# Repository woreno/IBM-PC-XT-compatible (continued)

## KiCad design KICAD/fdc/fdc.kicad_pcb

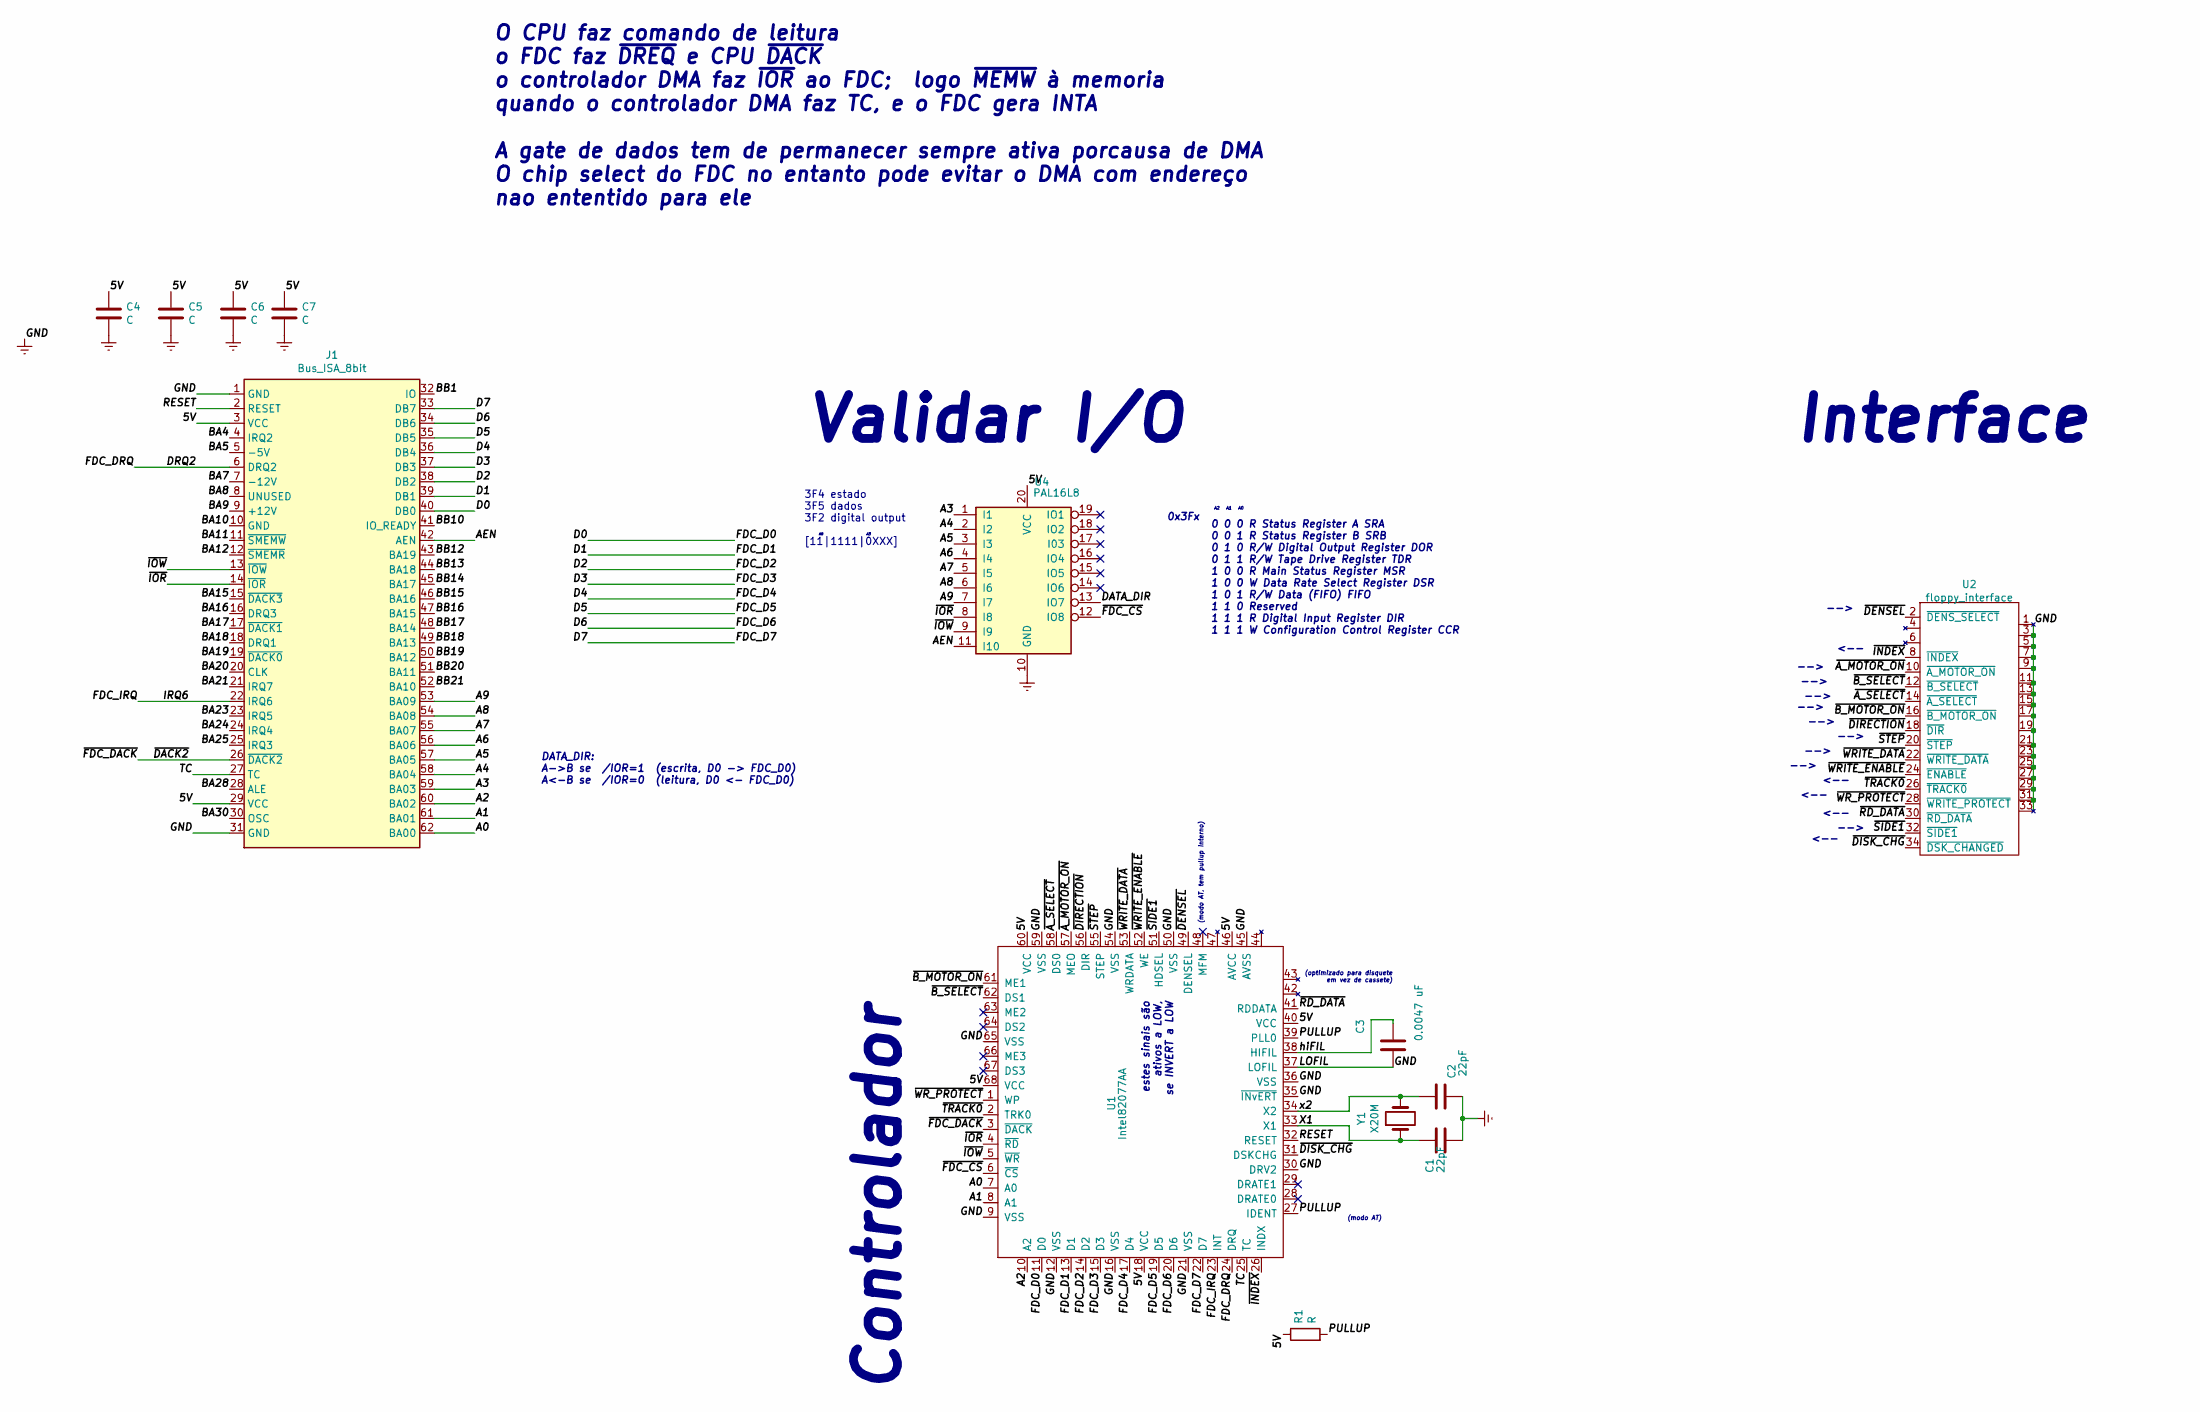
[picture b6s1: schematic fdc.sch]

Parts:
C1: 22pF; standard_2pins
C2: 22pF; standard_2pins_half
C3: 0.0047 uF; standard_2pins
C4, C5, C6: C; standard_2pins
C7: C; standard_2pins_half
J1: Bus_ISA_8bit; ISA_8bit_edge
R1: R; standard_2pins
U1: Intel82077AA; PLCC-68_SMD-Socket
U2: floppy_interface; PinSocket_2x17_P2.54mm_Vertical
U4: PAL16L8; standard_DIP_20pins_thin_body
Y1: X20M; standard_2pins_half

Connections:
/5V: C4.1, C5.1, C6.1, C7.1, J1.3 (VCC), J1.29 (VCC), R1.1, U1.18 (VCC), U1.40 (VCC), U1.46 (AVCC), U1.60 (VCC), U1.68 (VCC), U4.20 (VCC)
/A0: J1.62 (BA00), U1.7 (A0)
/A1: J1.61 (BA01), U1.8 (A1)
/A2: J1.60 (BA02), U1.10 (A2)
/A3: J1.59 (BA03), U4.1 (I1)
/A4: J1.58 (BA04), U4.2 (I2)
/A5: J1.57 (BA05), U4.3 (I3)
/A6: J1.56 (BA06), U4.4 (I4)
/A7: J1.55 (BA07), U4.5 (I5)
/A8: J1.54 (BA08), U4.6 (I6)
/A9: J1.53 (BA09), U4.7 (I7)
/AEN: J1.42 (AEN), U4.11 (I10)
/BA4: J1.4 (IRQ2)
/BA5: J1.5 (-5V)
/BA7: J1.7 (-12V)
/BA8: J1.8 (UNUSED)
/BA9: J1.9 (+12V)
/BA10: J1.10 (GND)
/BA11: J1.11 (~SMEMW)
/BA12: J1.12 (~SMEMR)
/BA15: J1.15 (~DACK3)
/BA16: J1.16 (DRQ3)
/BA17: J1.17 (~DACK1)
/BA18: J1.18 (DRQ1)
/BA19: J1.19 (~DACK0)
/BA20: J1.20 (CLK)
/BA21: J1.21 (IRQ7)
/BA23: J1.23 (IRQ5)
/BA24: J1.24 (IRQ4)
/BA25: J1.25 (IRQ3)
/BA28: J1.28 (ALE)
/BA30: J1.30 (OSC)
/BB1: J1.32 (IO)
/BB10: J1.41 (IO_READY)
/BB12: J1.43 (BA19)
/BB13: J1.44 (BA18)
/BB14: J1.45 (BA17)
/BB15: J1.46 (BA16)
/BB16: J1.47 (BA15)
/BB17: J1.48 (BA14)
/BB18: J1.49 (BA13)
/BB19: J1.50 (BA12)
/BB20: J1.51 (BA11)
/BB21: J1.52 (BA10)
/D0: J1.40 (DB0), U1.11 (D0)
/D1: J1.39 (DB1), U1.13 (D1)
/D2: J1.38 (DB2), U1.14 (D2)
/D3: J1.37 (DB3), U1.15 (D3)
/D4: J1.36 (DB4), U1.17 (D4)
/D5: J1.35 (DB5), U1.19 (D5)
/D6: J1.34 (DB6), U1.20 (D6)
/D7: J1.33 (DB7), U1.22 (D7)
/DATA_DIR: U4.13 (IO7)
/DRQ2: J1.6 (DRQ2), U1.24 (DRQ)
/FDC_IRQ: J1.22 (IRQ6), U1.23 (INT)
/PULLUP: R1.2, U1.27 (IDENT), U1.39 (PLL0)
/RESET: J1.2 (RESET), U1.32 (RESET)
/TC: J1.27 (TC), U1.25 (TC)
/X1: C1.1, U1.33 (X1), Y1.1
/hiFIL: C3.1, U1.38 (HIFIL)
/x2: C2.2, U1.34 (X2), Y1.2
/~A_MOTOR_ON: U1.57 (MEO), U2.10 (~A_MOTOR_ON)
/~A_SELECT: U1.58 (DS0), U2.14 (~A_SELECT)
/~B_MOTOR_ON: U1.61 (ME1), U2.16 (~B_MOTOR_ON)
/~B_SELECT: U1.62 (DS1), U2.12 (~B_SELECT)
/~DACK2: J1.26 (~DACK2), U1.3 (~DACK)
/~DENSEL: U1.49 (DENSEL), U2.2 (~DENS_SELECT)
/~DIRECTION: U1.56 (DIR), U2.18 (~DIR)
/~DISK_CHG: U1.31 (DSKCHG), U2.34 (~DSK_CHANGED)
/~FDC_CS: U1.6 (~CS), U4.12 (IO8)
/~INDEX: U1.26 (INDX), U2.8 (~INDEX)
/~IOR: J1.14 (~IOR), U1.4 (~RD), U4.8 (I8)
/~IOW: J1.13 (~IOW), U1.5 (~WR), U4.9 (I9)
/~RD_DATA: U1.41 (RDDATA), U2.30 (~RD_DATA)
/~SIDE1: U1.51 (HDSEL), U2.32 (~SIDE1)
/~STEP: U1.55 (STEP), U2.20 (~STEP)
/~TRACK0: U1.2 (TRK0), U2.26 (~TRACK0)
/~WRITE_DATA: U1.53 (WRDATA), U2.22 (~WRITE_DATA)
/~WRITE_ENABLE: U1.52 (WE), U2.24 (~ENABLE)
/~WR_PROTECT: U1.1 (WP), U2.28 (~WRITE_PROTECT)
Earth: C1.2, C2.1, C3.2, C4.2, C5.2, C6.2, C7.2, J1.1 (GND), J1.31 (GND), U1.9 (VSS), U1.12 (VSS), U1.16 (VSS), U1.21 (VSS), U1.30 (DRV2), U1.35 (~INvERT), U1.36 (VSS), U1.37 (LOFIL), U1.45 (AVSS), U1.50 (VSS), U1.54 (VSS), U1.59 (VSS), U1.65 (VSS), U2.1, U2.3, U2.5, U2.7, U2.9, U2.11, U2.13, U2.15, U2.17, U2.19, U2.21, U2.23, U2.25, U2.27, U2.29, U2.31, U2.33, U4.10 (GND)

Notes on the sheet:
0 0 0 R Status Register A SRA 0 0 1 R Status Register B SRB 0 1 0 R/W Digital Output Register DOR 0 1 1 R/W Tape Drive Register TDR 1 0 0 R Main Status Register MSR 1 0 0 W Data Rate Select Register DSR 1 0 1 R/W Data (FIFO) FIFO 1 1 0 Reserved 1 1 1 R Digital Input Register DIR 1 1 1 W Configurati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
A2 A1 A0
0x3Fx
(modo AT)
estes sinais são ativos a LOW, se INVERT a LOW
(modo AT, tem pullup interno)
(optimizado para disquete em vez de cassete)
3F4 estado 3F5 dados 3F2 digital output [11|1111|0XXX]
<--
-->
Controlador
Interface
Validar I/O
O CPU faz comando de leitura o FDC faz ~DREQ~ e CPU ~DACK~ o controlador DMA faz ~IOR~ ao FDC; logo ~MEMW~ à memoria quando o controlador DMA faz TC, e o FDC gera INTA A gate de dados tem de permanecer sempre ativa porcausa de DMA O chip select do FDC no entanto pode evitar o DMA com endereço nao e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
DATA_DIR: A->B se /IOR=1 (escrita, D0 -> FDC_D0) A<-B se /IOR=0 (leitura, D0 <- FDC_D0)

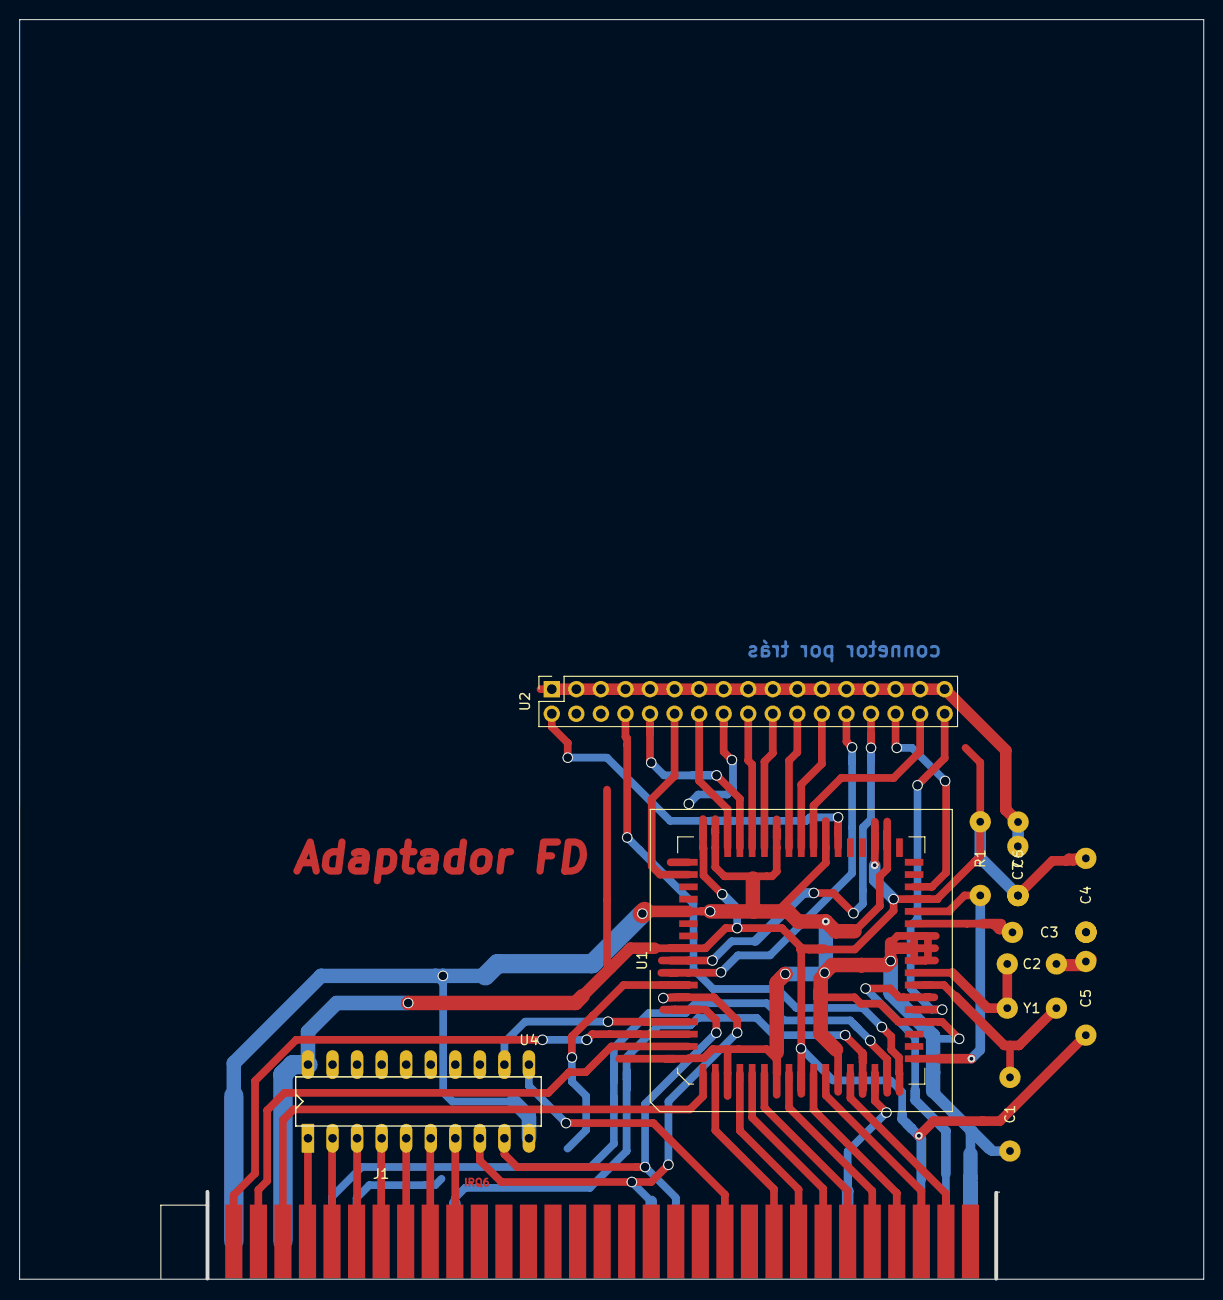
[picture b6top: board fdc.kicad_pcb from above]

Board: 2 copper layers, 122.5 x 130.3 mm, 13 parts (0 on the bottom side), 47 nets.

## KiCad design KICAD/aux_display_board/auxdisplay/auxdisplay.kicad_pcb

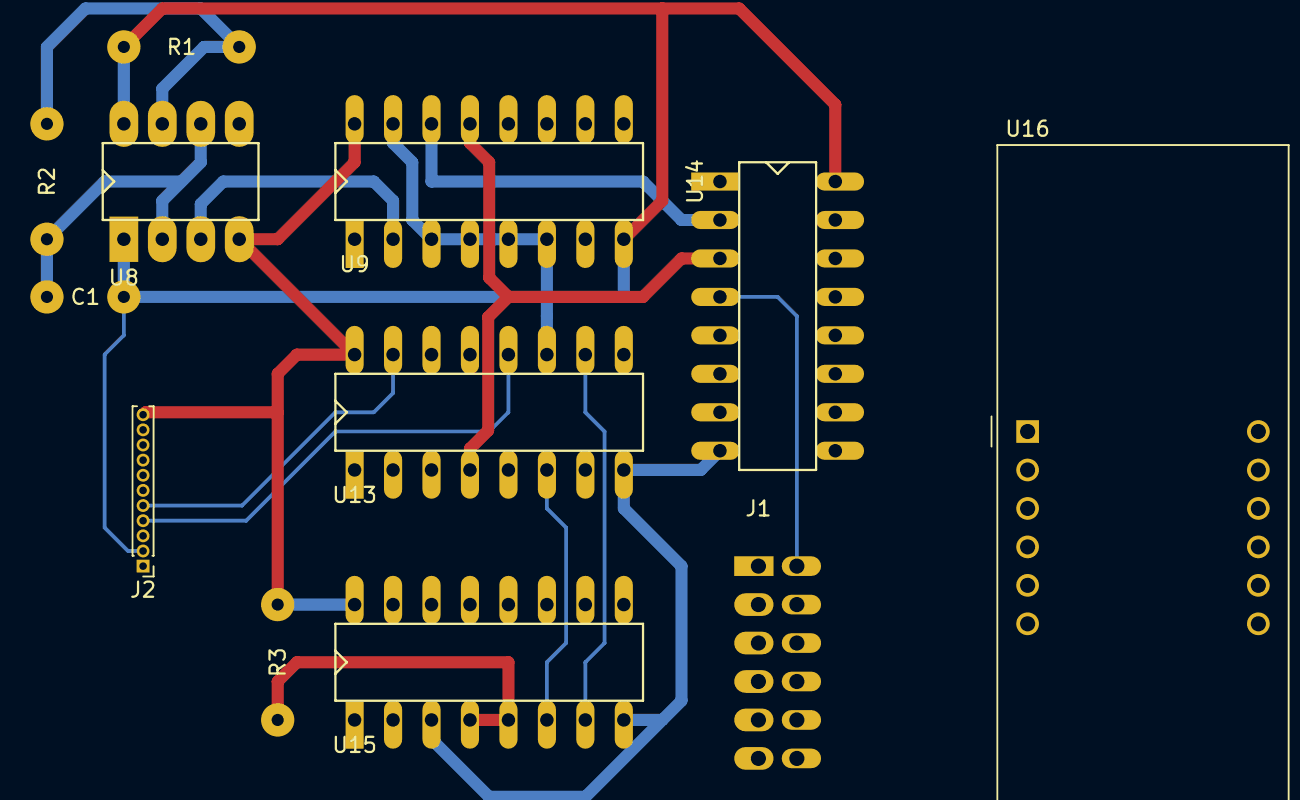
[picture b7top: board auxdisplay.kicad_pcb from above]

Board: 2 copper layers, 12 parts (0 on the bottom side), 30 nets.

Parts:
C1: C; standard_2pins_half
J1: Conn_02x06_Counter_Clockwise; Conector2x6_Oval_anticlock
J2: Conn_01x11_Female; PinHeader_1x11_P1.00mm_Vertical
R1, R2, R3: R; standard_2pins
U8: 555; standard_DIP_8pins
U9: 74LS161; standard_DIP_16OvalPins
U13: 74LS670; standard_DIP_16OvalPins
U14: 74LS139; standard_DIP_16OvalPins
U15: DM9368; standard_DIP_16OvalPins
U16: CC56-12SRWA; CA56-12SRWA

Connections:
/5V: J2.11, R1.1, R3.2, U8.4, U8.8, U9.16, U13.16, U14.16, U15.16
/A0: J2.9, U13.14
/A1: J2.10, U13.13
/D0: J2.5, U13.15
/D1: J2.6, U13.1
/D2: J2.7, U13.2
/D3: J2.8, U13.3
/dispA_11: J1.11, U15.13, U16.11
/dispB_7: J1.7, U15.12, U16.7
/dispC0: U9.14, U13.5, U14.2
/dispC1: U9.13, U13.4, U14.3
/dispCLK~: U8.3, U9.2
/dispC_4: J1.4, U15.11, U16.4
/dispD_2: J1.2, U15.10, U16.2
/dispDigit0_12: J1.12, U14.4, U16.6
/dispDigit1_9: J1.9, U14.5, U16.8
/dispDigit2_8: J1.8, U14.6, U16.9
/dispDigit3_6: J1.6, U14.7, U16.12
/dispE_1: J1.1, U15.9, U16.1
/dispF_10: J1.10, U15.15, U16.10
/dispG_5: J1.5, U15.14, U16.5
/dispPullup: R3.1, U9.1, U15.4, U15.5
/~dispCS: J2.4, U13.12
Earth: C1.2, J1.3, J2.2, U8.1, U9.3, U9.4, U9.5, U9.6, U9.8, U9.15, U13.8, U13.11, U14.8, U15.3, U15.8, U16.3
unnamed: C1.1, R2.2, U8.2, U8.6
unnamed: R1.2, R2.1, U8.7
unnamed: U13.6, U15.6
unnamed: U13.7, U15.2
unnamed: U13.9, U15.1
unnamed: U13.10, U15.7

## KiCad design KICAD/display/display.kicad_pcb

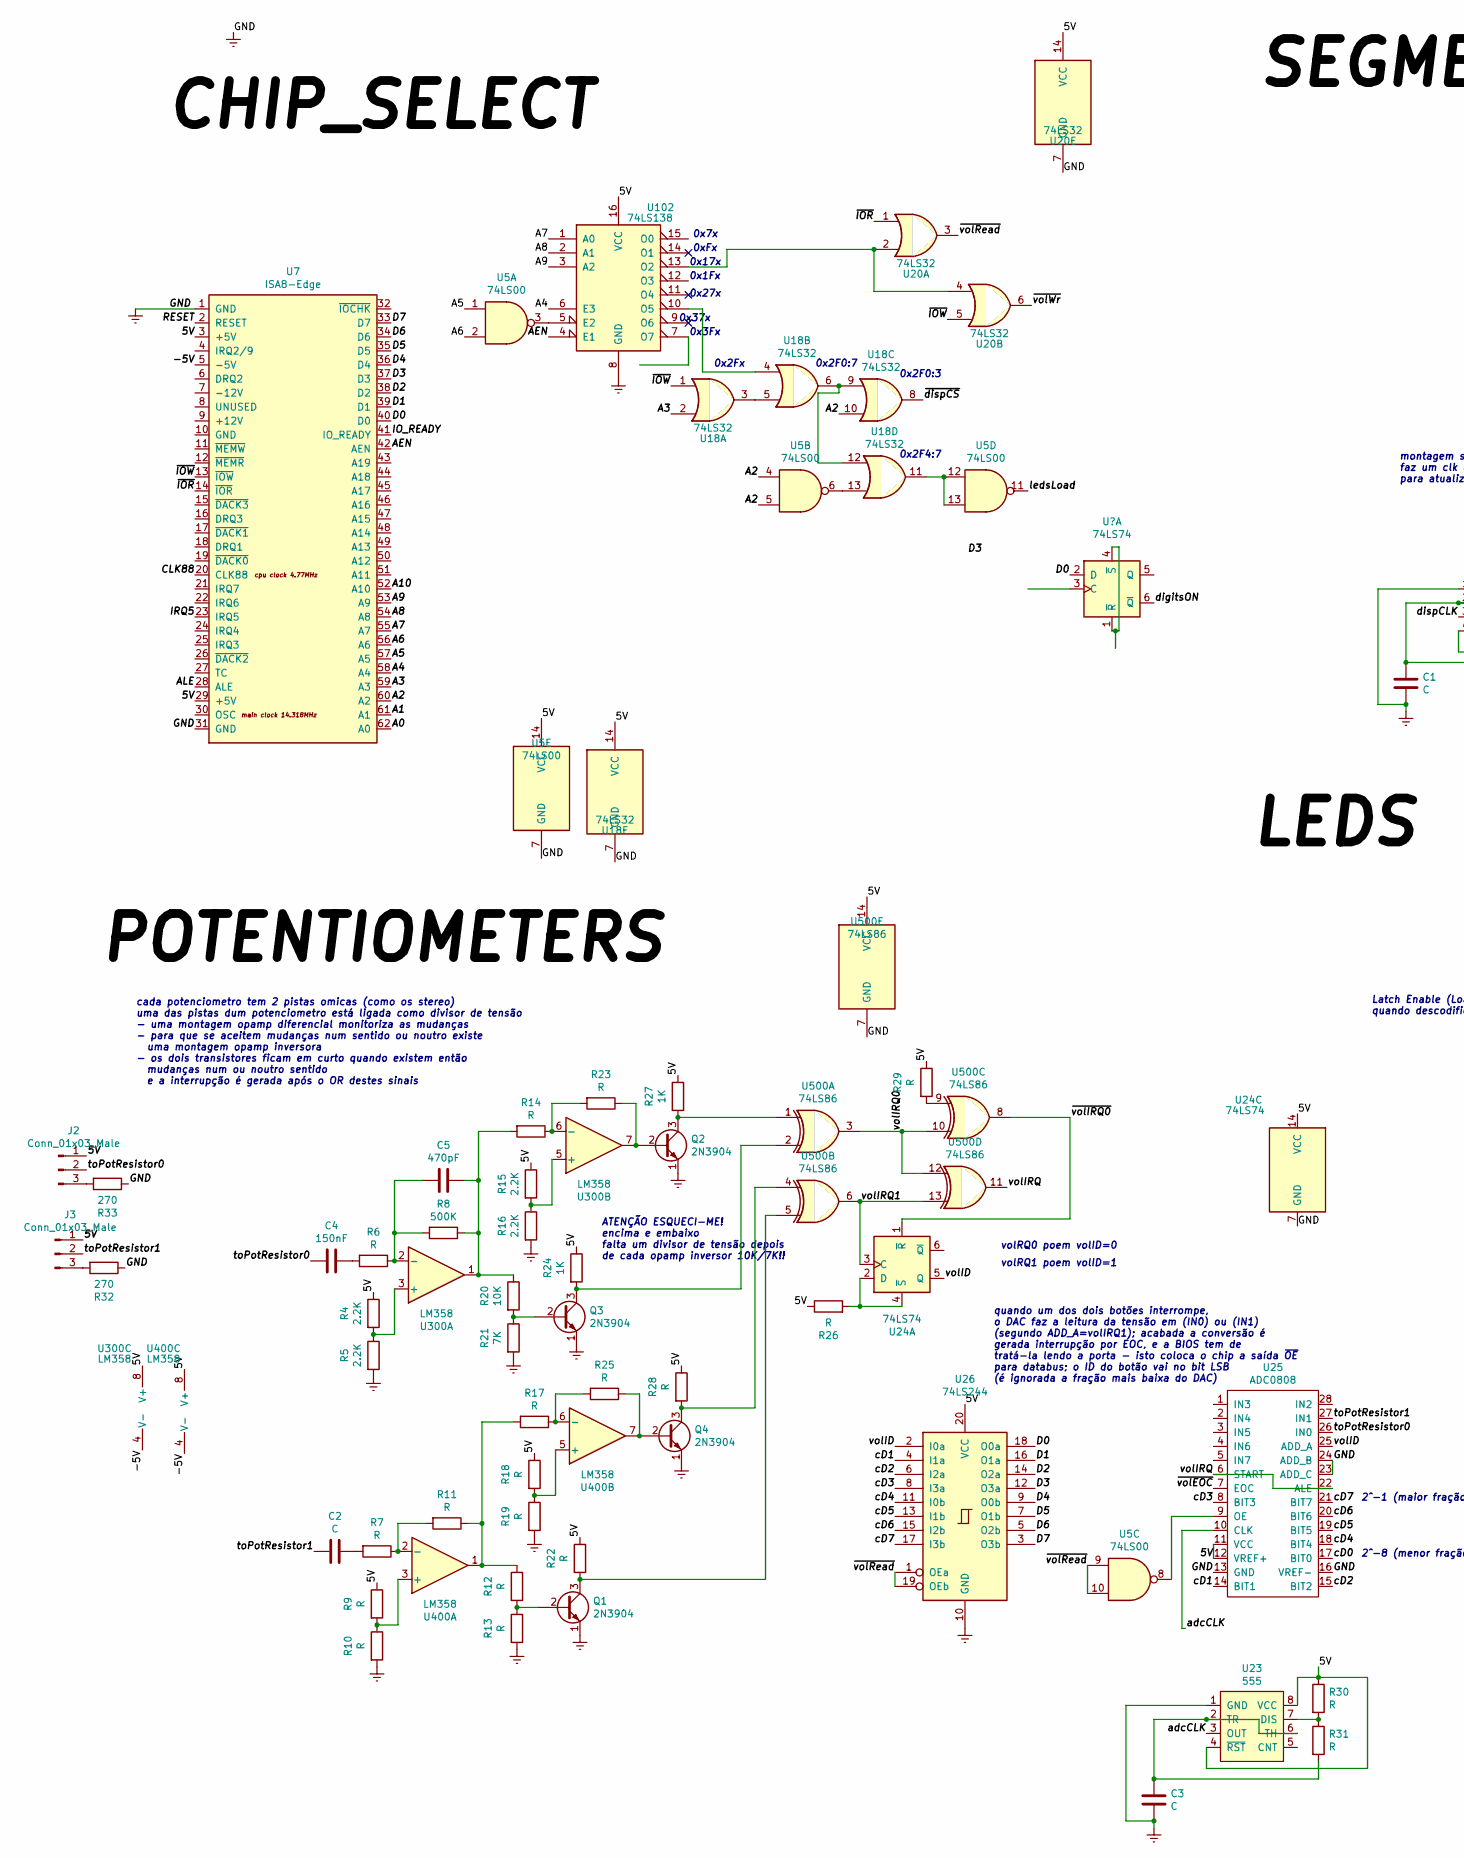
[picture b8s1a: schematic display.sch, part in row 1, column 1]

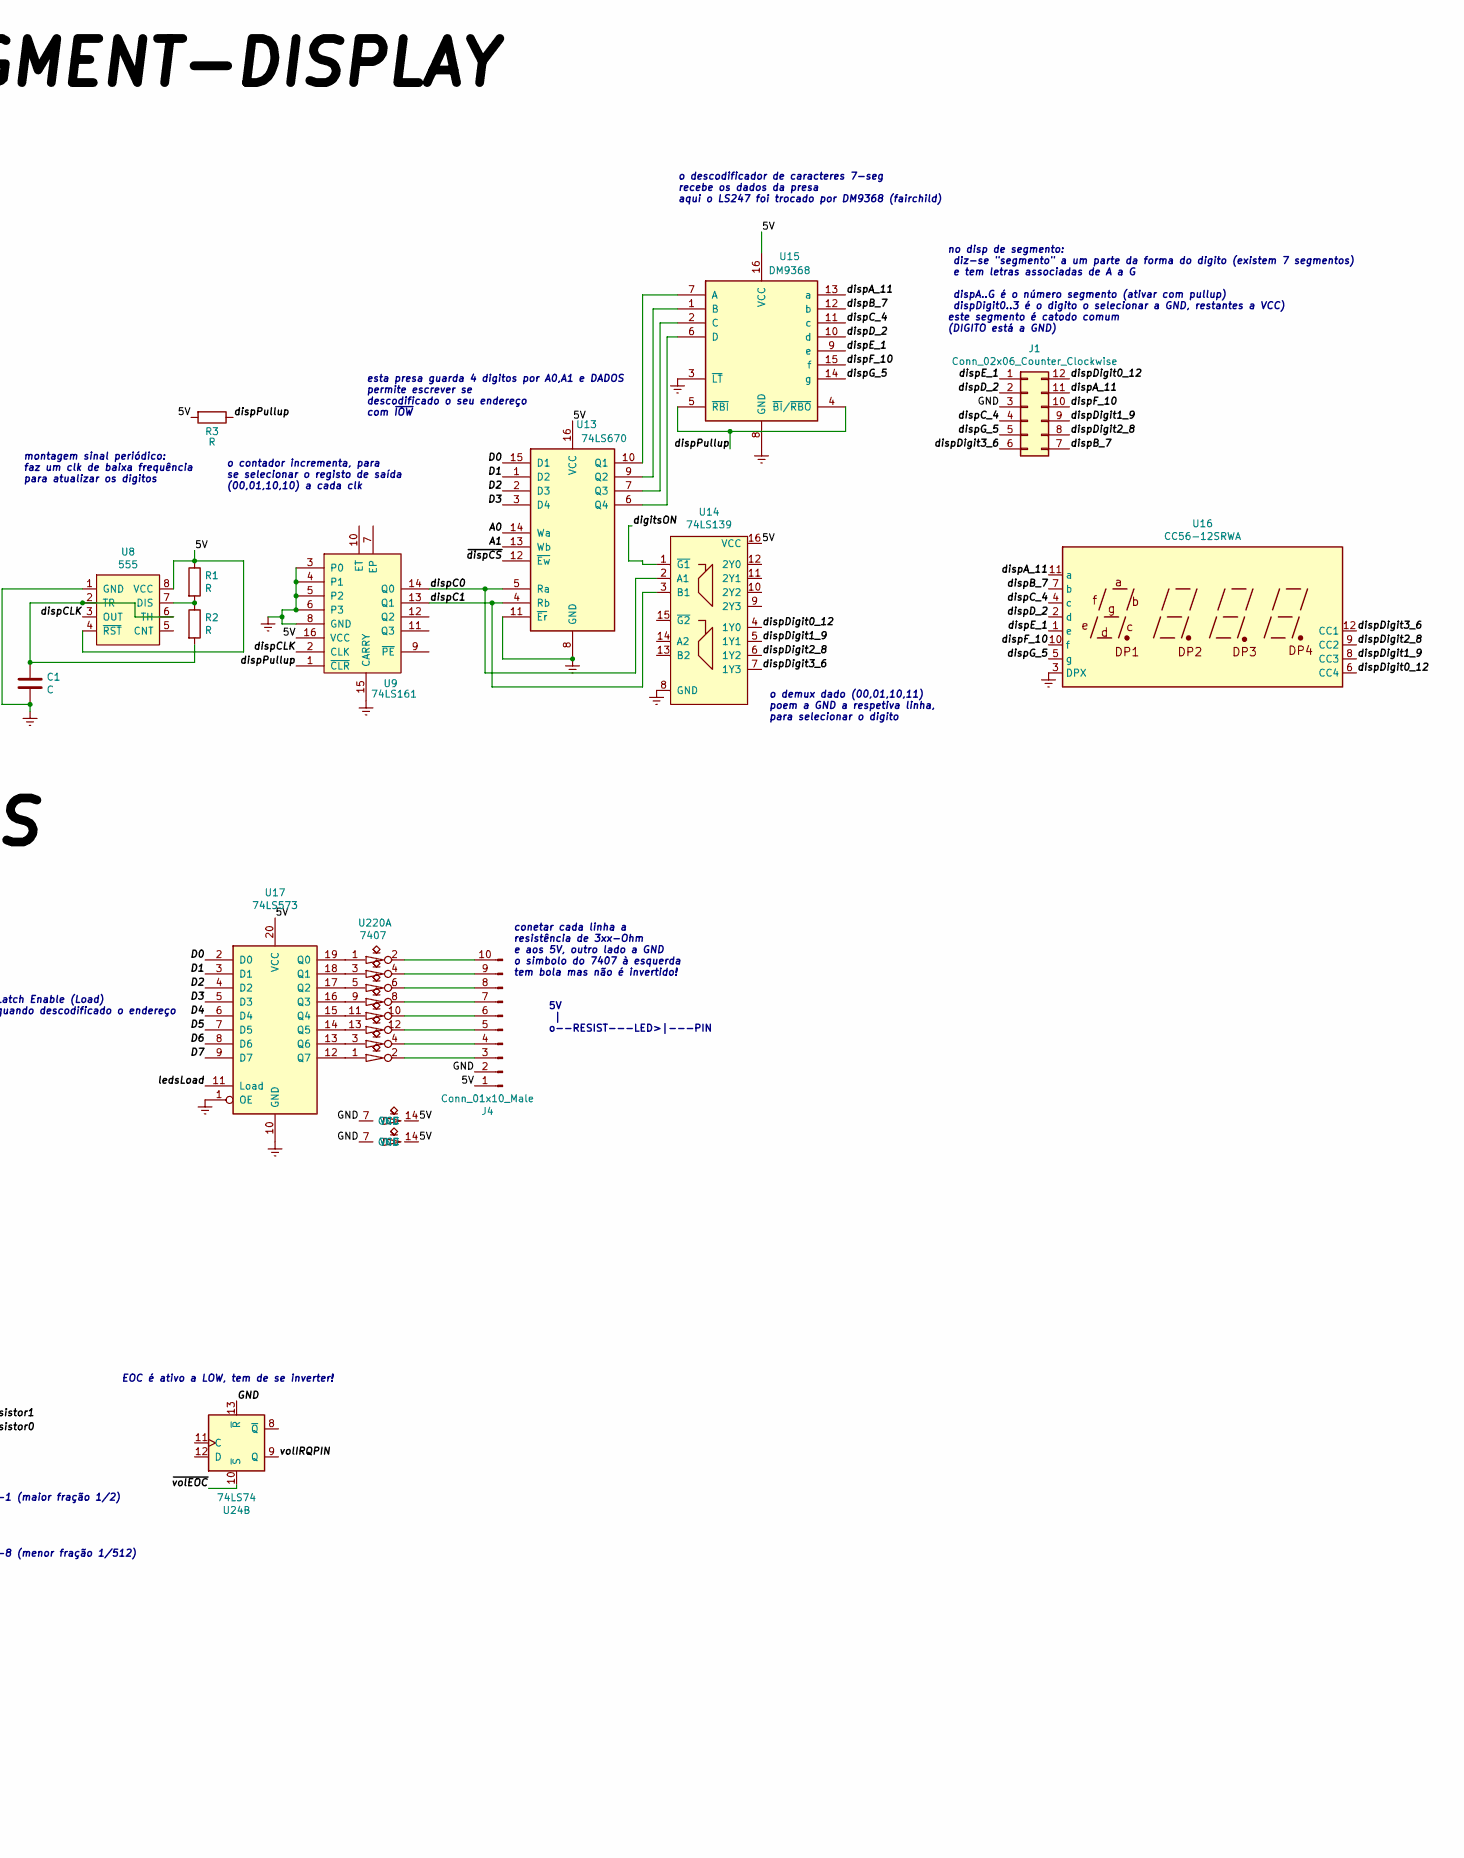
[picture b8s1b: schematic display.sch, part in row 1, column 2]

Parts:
C1, C2, C3: C; standard_2pins_half
C4: 150nF; standard_2pins_half
C5: 470pF
J1: Conn_02x06_Counter_Clockwise; Conector2x6_Oval_anticlock
J2, J3: Conn_01x03_Male; PinHeader_1x03_P2.54mm_Vertical
J4: Conn_01x10_Male; Conector2x5_Oval_alternado
Q1, Q2, Q3, Q4: 2N3904; TO-92_Inline
R1, R2, R3, R6, R7, R9, R10, R11, R12, R13, R14, R17, R18, R19, R22, R23, R25, R26, R28, R29, R30, R31: R; standard_2pins
R4, R5, R15, R16: 2.2K; standard_2pins
R8: 500K; standard_2pins
R20: 10K; standard_2pins
R21: 7K; standard_2pins
R24, R27: 1K; standard_2pins
R32, R33: 270
U5: 74LS00; standard_DIP_14OvalPins
U7: ISA8-Edge; ISA_8bit_edge
U8, U23: 555; standard_DIP_8pins
U9: 74LS161; standard_DIP_16OvalPins
U13: 74LS670; standard_DIP_16OvalPins
U14: 74LS139; standard_DIP_16OvalPins
U15: DM9368; standard_DIP_16OvalPins
U16: CC56-12SRWA; CA56-12SRWA
U17: 74LS573; standard_DIP_20pins_thin_body
U18, U20: 74LS32; standard_DIP_14OvalPins
U24: 74LS74; standard_DIP_14OvalPins
U25: ADC0808; standard_DIP_28pins_thin_doubleBody
U26: 74LS244; standard_DIP_20pins_thin_body
U102: 74LS138; standard_DIP_16OvalPins
U220, U221: 7407; standard_DIP_14OvalPins
U300, U400: LM358; LM386
U500: 74LS86; standard_DIP_14OvalPins

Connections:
/5V: J2.1, J3.1, J4.1, R1.1, R3.2, R4.1, R9.1, R15.1, R18.1, R22.1, R24.1, R26.1, R27.1, R28.1, R29.1, R30.1, U5.14 (VCC), U7.3 (+5V), U7.29 (+5V), U8.4 (~RST), U8.8 (VCC), U9.16 (VCC), U13.16 (VCC), U14.16 (VCC), U15.16 (VCC), U17.20 (VCC), U18.14 (VCC), U20.14 (VCC), U23.4 (~RST), U23.8 (VCC), U24.14 (VCC), U25.11 (VCC), U25.12 (VREF+), U26.20 (VCC), U102.16 (VCC), U220.14 (VCC), U221.14 (VCC), U300.8 (V+), U400.8 (V+), U500.14 (VCC)
/-5V: U7.5 (-5V), U300.4 (V-), U400.4 (V-)
/A0: U7.62 (A0), U13.14 (Wa)
/A1: U7.61 (A1), U13.13 (Wb)
/A2: U5.4, U5.5, U7.60 (A2), U18.10
/A3: U7.59 (A3), U18.2
/A4: U7.58 (A4), U102.6 (E3)
/A5: U5.1, U7.57 (A5)
/A6: U5.2, U7.56 (A6)
/A7: U7.55 (A7), U102.1 (A0)
/A8: U7.54 (A8), U102.2 (A1)
/A9: U7.53 (A9), U102.3 (A2)
/A10: U7.52 (A10)
/AEN: U7.42 (AEN), U102.4 (E1)
/ALE: U7.28 (ALE)
/CLK88: U7.20 (CLK88)
/D0: U7.40 (D0), U13.15 (D1), U17.2 (D0), U26.18 (O0a)
/D1: U7.39 (D1), U13.1 (D2), U17.3 (D1), U26.16 (O1a)
/D2: U7.38 (D2), U13.2 (D3), U17.4 (D2), U26.14 (O2a)
/D3: U7.37 (D3), U13.3 (D4), U17.5 (D3), U26.12 (O3a)
/D4: U7.36 (D4), U17.6 (D4), U26.9 (O0b)
/D5: U7.35 (D5), U17.7 (D5), U26.7 (O1b)
/D6: U7.34 (D6), U17.8 (D6), U26.5 (O2b)
/D7: U7.33 (D7), U17.9 (D7), U26.3 (O3b)
/IO_READY: U7.41 (IO_READY)
/IRQ5: U7.23 (IRQ5)
/RESET: U7.2 (RESET)
/adcCLK: U23.3 (OUT), U25.10 (CLK)
/cD0: U25.17 (BIT0)
/cD1: U25.14 (BIT1), U26.4 (I1a)
/cD2: U25.15 (BIT2), U26.6 (I2a)
/cD3: U25.8 (BIT3), U26.8 (I3a)
/cD4: U25.18 (BIT4), U26.11 (I0b)
/cD5: U25.19 (BIT5), U26.13 (I1b)
/cD6: U25.20 (BIT6), U26.15 (I2b)
/cD7: U25.21 (BIT7), U26.17 (I3b)
/dispA_11: J1.11, U15.13 (a), U16.11 (a)
/dispB_7: J1.7, U15.12 (b), U16.7 (b)
/dispC0: U9.14 (Q0), U13.5 (Ra), U14.2 (A1)
/dispC1: U9.13 (Q1), U13.4 (Rb), U14.3 (B1)
/dispCLK~: U8.3 (OUT), U9.2 (CLK)
/dispC_4: J1.4, U15.11 (c), U16.4 (c)
/dispD_2: J1.2, U15.10 (d), U16.2 (d)
/dispDigit0_12: J1.12, U14.4 (1Y0), U16.6 (CC4)
/dispDigit1_9: J1.9, U14.5 (1Y1), U16.8 (CC3)
/dispDigit2_8: J1.8, U14.6 (1Y2), U16.9 (CC2)
/dispDigit3_6: J1.6, U14.7 (1Y3), U16.12 (CC1)
/dispE_1: J1.1, U15.9 (e), U16.1 (e)
/dispF_10: J1.10, U15.15 (f), U16.10 (f)
/dispG_5: J1.5, U15.14 (g), U16.5 (g)
/dispPullup: R3.1, U9.1 (~CLR), U15.4 (~BI~/~RBO), U15.5 (~RBI)
/ledsLoad: U5.11, U17.11 (Load)
/toPotResistor0: C4.2, J2.2, U25.26 (IN0)
/toPotResistor1: C2.2, J3.2, U25.27 (IN1)
/volID: U24.5 (Q), U25.25 (ADD_A), U26.2 (I0a)
/volIRQ: U25.6 (START), U25.22 (ALE), U500.11
/volIRQ0: U500.3, U500.10, U500.12
/volIRQ1: U24.3 (C), U500.6, U500.13
/volIRQPIN: U24.9 (Q)
/~IOR: U7.14 (~IOR), U20.1
/~IOW: U7.13 (~IOW), U18.1, U20.5
/~dispCS: U13.12 (~Ew), U18.8
/~volEOC: U24.10 (~S), U25.7 (EOC)
/~volIRQ0: U24.1 (~R), U500.8
/~volRead: U5.9, U5.10, U20.3, U26.1 (OEa), U26.19 (OEb)
/~volWr: U20.6
unnamed: C1.1, R2.2, U8.2 (TR), U8.6 (TH)
unnamed: C2.1, R7.2
unnamed: C3.1, R31.2, U23.2 (TR), U23.6 (TH)
unnamed: C4.1, R6.2
unnamed: C5.1, R8.1, R14.2, R20.1, U300.1
unnamed: C5.2, R6.1, R8.2, U300.2 (-)
unnamed: J2.3, R33.2
unnamed: J3.3, R32.2
unnamed: J4.3, U221.2
unnamed: J4.4, U221.4
unnamed: J4.5, U220.12
unnamed: J4.6, U220.10
unnamed: J4.7, U220.8
unnamed: J4.8, U220.6
unnamed: J4.9, U220.4
unnamed: J4.10, U220.2
unnamed: Q1.2 (B), R12.2, R13.1
unnamed: Q1.3 (C), R22.2, U500.5
unnamed: Q2.2 (B), R23.1, U300.7
unnamed: Q2.3 (C), R27.2, U500.1
unnamed: Q3.2 (B), R20.2, R21.1
unnamed: Q3.3 (C), R24.2, U500.2
unnamed: Q4.2 (B), R25.1, U400.7
unnamed: Q4.3 (C), R28.2, U500.4
unnamed: R1.2, R2.1, U8.7 (DIS)
unnamed: R4.2, R5.1, U300.3 (+)
unnamed: R9.2, R10.1, U400.3 (+)
unnamed: R11.1, R12.1, R17.2, U400.1
unnamed: R7.1, R11.2, U400.2 (-)
unnamed: R14.1, R23.2, U300.6 (-)
unnamed: R15.2, R16.1, U300.5 (+)
unnamed: R17.1, R25.2, U400.6 (-)
unnamed: R18.2, R19.1, U400.5 (+)
unnamed: R26.2, U24.2 (D), U24.4 (~S)
unnamed: R29.2, U500.9
unnamed: R30.2, R31.1, U23.7 (DIS)
unnamed: U13.6 (Q4), U15.6 (D)
unnamed: U13.7 (Q3), U15.2 (C)
unnamed: U13.9 (Q2), U15.1 (B)
unnamed: U13.10 (Q1), U15.7 (A)
unnamed: U17.12 (Q7), U221.1
unnamed: U17.13 (Q6), U221.3
unnamed: U17.14 (Q5), U220.13
unnamed: U17.15 (Q4), U220.11
unnamed: U17.16 (Q3), U220.9
unnamed: U17.17 (Q2), U220.5
unnamed: U17.18 (Q1), U220.3
unnamed: U17.19 (Q0), U220.1
unnamed: U18.3, U18.5
unnamed: U5.12, U5.13, U18.11
unnamed: U18.6, U18.9, U18.12
unnamed: U5.6, U18.13
unnamed: U5.8, U25.9 (OE)
unnamed: U5.3, U102.5 (E2)
unnamed: U18.4, U102.10 (O5)
unnamed: U20.2, U20.4, U102.13 (O2)

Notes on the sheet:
montagem sinal periódico: faz um clk de baixa frequência para atualizar os digitos
o contador incrementa, para se selecionar o registo de saída (00,01,10,10) a cada clk
esta presa guarda 4 digitos por A0,A1 e DADOS permite escrever se descodificado o seu endereço com ~IOW
o demux dado (00,01,10,11) poem a GND a respetiva linha, para selecionar o digito
0x2Fx
0x1Fx
o descodificador de caracteres 7-seg recebe os dados da presa aqui o LS247 foi trocado por DM9368 (fairchild)
0x2F4:7
0x2F0:7
2^-1 (maior fração 1/2)
2^-8 (menor fração 1/512)
quando um dos dois botões interrompe, o DAC faz a leitura da tensão em (IN0) ou (IN1) (segundo ADD_A=volIRQ1); acabada a conversão é gerada interrupção por EOC, e a BIOS tem de tratá-la lendo a porta - isto coloca o chip a saída ~OE~ para databus; o ID do botão vai no bit LSB (é ignorada a fração m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
no disp de segmento: diz-se "segmento" a um parte da forma do digito (existem 7 segmentos) e tem letras associadas de A a G dispA..G é o número segmento (ativar com pullup) dispDigit0..3 é o digito o selecionar a GND, restantes a VCC) este segmento é catodo comum (DIGITO está a GND)
cada potenciometro tem 2 pistas omicas (como os stereo) uma das pistas dum potenciometro está ligada como divisor de tensão - uma montagem opamp diferencial monitoriza as mudanças - para que se aceitem mudanças num sentido ou noutro existe uma montagem opamp inversora - os dois transistores ficam e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
5V | o--RESIST---LED>|---PIN
conetar cada linha a resistência de 3xx-Ohm e aos 5V, outro lado a GND o simbolo do 7407 à esquerda tem bola mas não é invertido!
0x17x
0xFx
0x27x
0x37x
volRQ0 poem volID=0
volRQ1 poem volID=1
0x7x
Latch Enable (Load) quando descodificado o endereço
0x2F0:3
ATENÇÃO ESQUECI-ME! encima e embaixo falta um divisor de tensão depois de cada opamp inversor 10K/7K!!
EOC é ativo a LOW, tem de se inverter!
0x3Fx

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
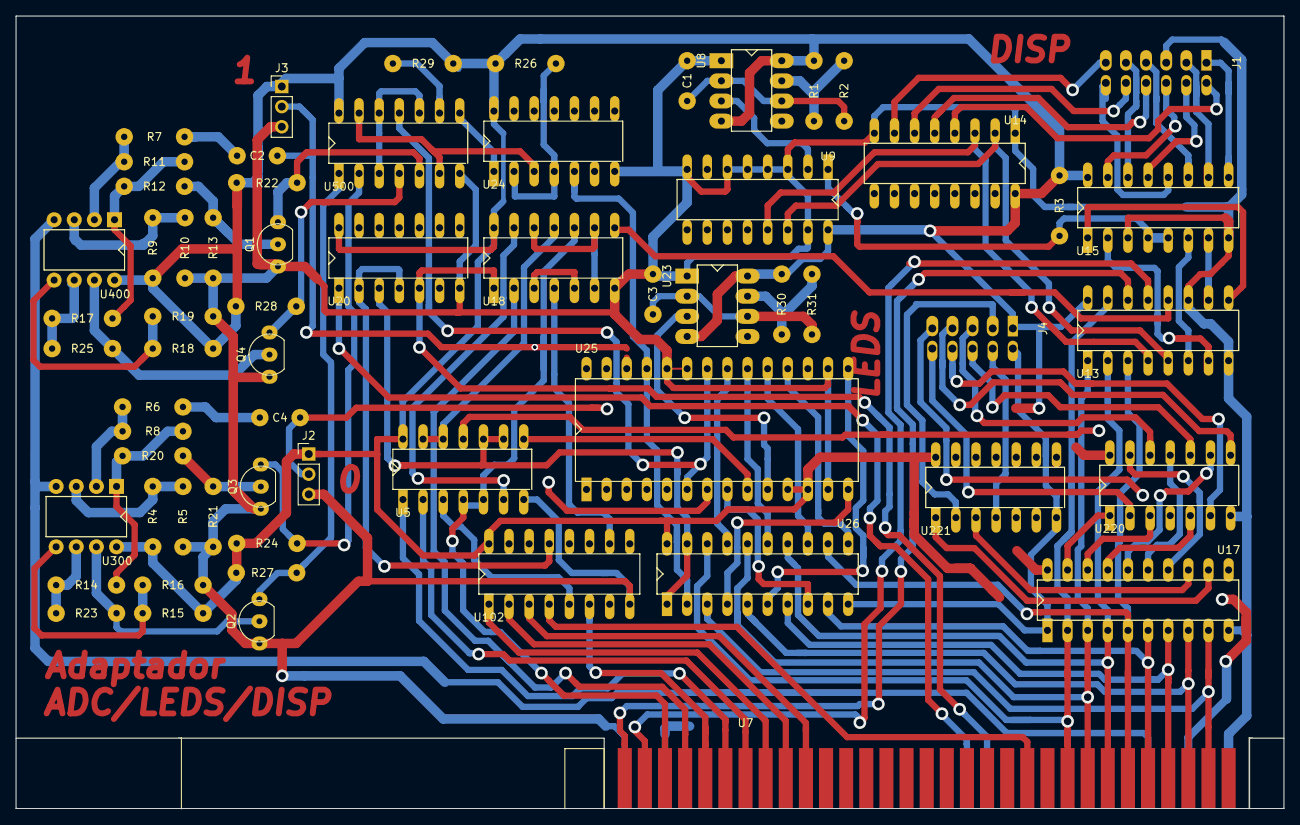
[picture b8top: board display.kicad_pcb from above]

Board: 2 copper layers, 160.0 x 100.0 mm, 63 parts (0 on the bottom side), 112 nets.

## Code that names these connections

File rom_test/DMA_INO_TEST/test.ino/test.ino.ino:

#define DMA_CHAN0_ADDR	0
#define DMA_CHAN0_CNT	1
#define DMA_STATUS		8
#define DMA_CMD			8	
#define DMA_REQUEST		9	
#define DMA_MASK_CHAN	10	
#define DMA_MODES		11	
#define DMA_REG16_RESET	12	
#define DMA_RESET		13
#define DMA_ERASEMASK	14
#define DMA_MASK		15 
#define M_WaitDMA
#define W8				unsigned char

#define SET_PORT_OUTPUT(W_)    DDR##W_=0xFF;
#define SET_PORT_INPUT(W_)	   DDR##W_=0x0; PORT##W_=0x0; 

//PA0:7 XD7:0 databus
//PC0:3 XA0:3 addr
//PB0:3 0:DREQ0,1:CS,2:XIOW

#define DREQ_TOGGLE PORTB^=1;
#define RST_LO		  PORTB=0;
#define RST_HI		  PORTB=8;
#define CS_XIOW_LO  PORTB&=~6;
#define CS_HI       PORTB|=2;
#define XIOW_HI     PORTB|=1;

#define DATA_PORT PORTA
#define ADDR_PORT PORTC
#define CTRL_PORT PORTB
#define W8_BIT(V,START)         (((V)>>(START))&1)          
#define W8_REVERSE(W)         (W8_BIT(W,7)|(W8_BIT(W,6)<<1)|(W8_BIT(W,5)<<2)|(W8_BIT(W,4)<<3)|(W8_BIT(W,3)<<4)|(W8_BIT(W,2)<<5)|(W8_BIT(W,1)<<6)|(W8_BIT(W,0)<<7))

void out(W8 addr_,W8 data_)
{
  data_ = W8_REVERSE(data_);
	ADDR_PORT = addr_;
	DATA_PORT = data_;
  delay(20); 
	CS_XIOW_LO
	delayMicroseconds(10); 
	XIOW_HI
  delayMicroseconds(10); 
  CS_HI
  delay(20); 
}
void setup() 
{
	SET_PORT_OUTPUT(A)
	SET_PORT_OUTPUT(B)
	SET_PORT_OUTPUT(C)
	RST_HI
	delay(200);
	RST_LO
  DREQ_TOGGLE
}
 
void loop() 
{

  W8 al = 1;

  
  al = 0;
  // configurar DMA
  out(DMA_RESET, al);
  M_WaitDMA
  
  // configurar DMA
  out(DMA_REG16_RESET, al);
  M_WaitDMA
  out(DMA_CHAN0_ADDR, al);
  M_WaitDMA
  out(DMA_CHAN0_ADDR, al);
  M_WaitDMA

  al = 0xFF;
  out(DMA_REG16_RESET, al);
  M_WaitDMA
  out(DMA_CHAN0_CNT, al);
  M_WaitDMA
  out(DMA_CHAN0_CNT, al);
  M_WaitDMA

  al = 0x58;
  out(DMA_MODES, al);
  M_WaitDMA

  al = 0xFE;
  out(DMA_MASK, al);
  M_WaitDMA

  al = 0;
  out(DMA_MASK_CHAN, al);
  M_WaitDMA

  out(DMA_CMD, al);
  M_WaitDMA

  SET_PORT_INPUT(A)
  SET_PORT_INPUT(C)
	// ligar DREQ
	while(1)	
	{
		DREQ_TOGGLE
		delay(20); 
		DREQ_TOGGLE
		delay(20); 
	}
}
